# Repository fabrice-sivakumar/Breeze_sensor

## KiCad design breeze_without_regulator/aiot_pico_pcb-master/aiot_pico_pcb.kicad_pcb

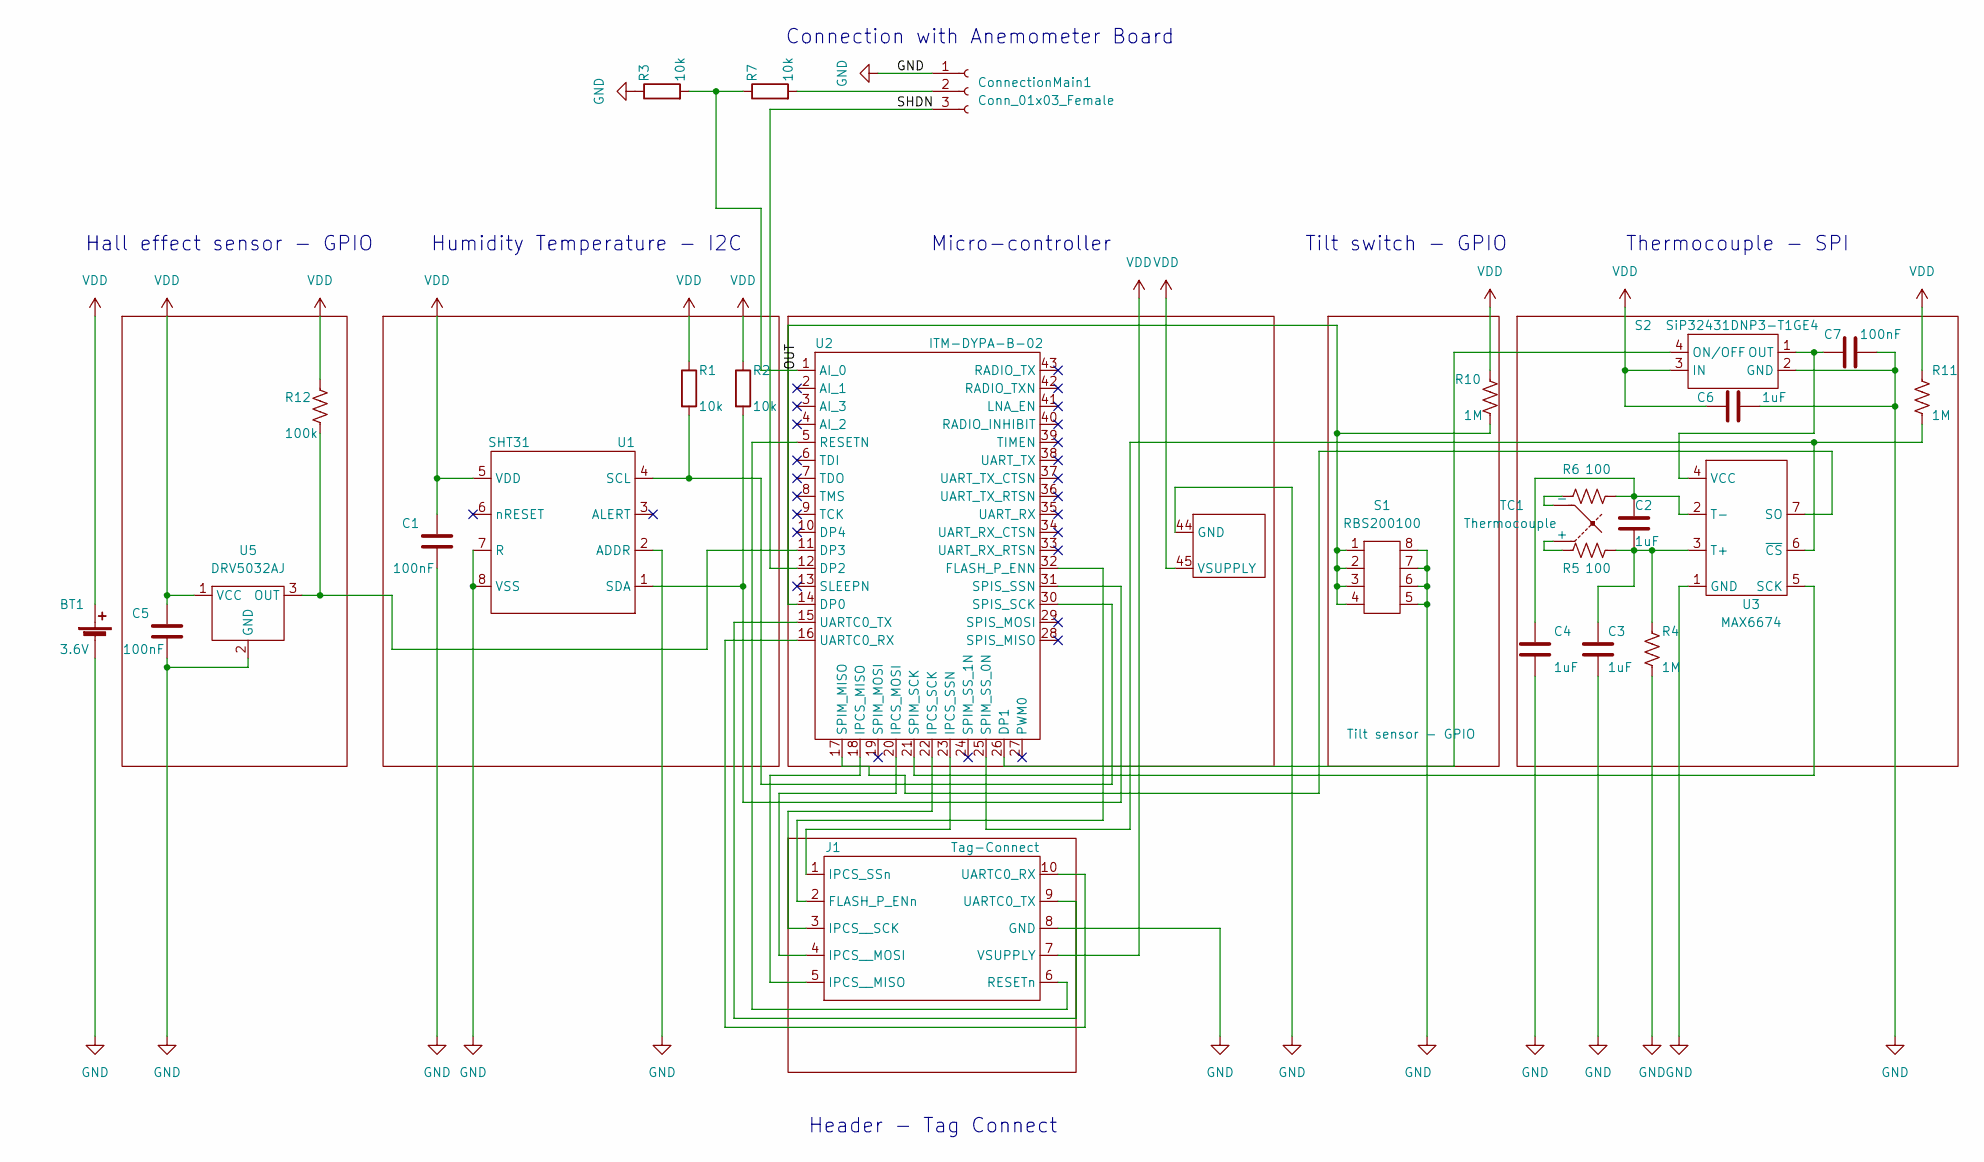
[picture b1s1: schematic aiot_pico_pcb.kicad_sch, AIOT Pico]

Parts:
BT1: 3.6V; BatteryHolder_Keystone_2460_1xAA
C1, C5, C7: 100nF; C_0603_1608Metric
C2, C3, C4, C6: 1uF; C_0603_1608Metric
ConnectionMain1: Conn_01x03_Female; PinSocket_1x03_P2.54mm_Vertical
J1: Tag-Connect; tag-connect_10_pins_no_hooks
R1, R2, R3, R7: 10k; R_0603_1608Metric
R4, R10, R11: 1M; R_0603_1608Metric
R5, R6: 100; R_0603_1608Metric
R12: 100k; R_0603_1608Metric
S1: RBS200100
S2: SiP32431DNP3-T1GE4; TDFN4_1.2mmx1.6mm
TC1: Thermocouple; Thermocouple_Connector_PCC-SMP-K
U1: SHT31; sht_31
U2: ITM-DYPA-B-02; dusty_pcb_ant
U3: MAX6674; SOIC-7-8_W3.9mm
U5: DRV5032AJ; TO-92-3

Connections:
/OUT: R3.2, R7.1, U2.1 (AI_0)
/SHDN: ConnectionMain1.3, U2.12 (DP2)
GND: BT1.2 (-), C1.2, C3.2, C4.2, C5.2, C6.2, C7.1, ConnectionMain1.1, J1.8 (GND), R3.1, R4.2, S1.5, S1.6, S1.7, S1.8, S2.2 (GND), U1.2 (ADDR), U1.7 (R), U1.8 (VSS), U2.44 (GND), U3.1 (GND), U5.2 (GND)
unnamed: C2.1, C4.1, R6.2, U3.2 (T-)
unnamed: C2.2, C3.1, R4.1, R5.2, U3.3 (T+)
unnamed: C7.2, S2.1 (OUT), U3.4 (VCC)
unnamed: ConnectionMain1.2, R7.2
unnamed: J1.1 (IPCS_SSn), U2.23 (IPCS_SSN)
unnamed: J1.2 (FLASH_P_ENn), U2.32 (FLASH_P_ENN)
unnamed: J1.3 (IPCS__SCK), U2.22 (IPCS_SCK)
unnamed: J1.4 (IPCS__MOSI), U2.20 (IPCS_MOSI)
unnamed: J1.5 (IPCS__MISO), U2.18 (IPCS_MISO)
unnamed: J1.6 (RESETn), U2.5 (RESETN)
unnamed: J1.9 (UARTC0_TX), U2.15 (UARTC0_TX)
unnamed: J1.10 (UARTC0_RX), U2.16 (UARTC0_RX)
unnamed: R1.2, U1.4 (SCL), U2.30 (SPIS_SCK)
unnamed: R2.2, U1.1 (SDA), U2.31 (SPIS_SSN)
unnamed: R5.1, TC1.1 (+)
unnamed: R6.1, TC1.2 (-)
unnamed: R10.2, S1.1, S1.2, S1.3, S1.4, U2.14 (DP0)
unnamed: R11.2, U2.25 (SPIM_SS_0N), U3.6 (~CS)
unnamed: R12.2, U2.11 (DP3), U5.3 (OUT)
unnamed: S2.4 (ON/OFF), U2.26 (DP1)
unnamed: U2.17 (SPIM_MISO), U3.7 (SO)
unnamed: U2.21 (SPIM_SCK), U3.5 (SCK)
VDD: BT1.1 (+), C1.1, C5.1, C6.1, J1.7 (VSUPPLY), R1.1, R2.1, R10.1, R11.1, R12.1, S2.3 (IN), U1.5 (VDD), U2.45 (VSUPPLY), U5.1 (VCC)

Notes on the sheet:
Thermocouple - SPI
Hall effect sensor - GPIO
Connection with Anemometer Board
Tilt switch - GPIO
Humidity Temperature - I2C
Micro-controller
Header - Tag Connect

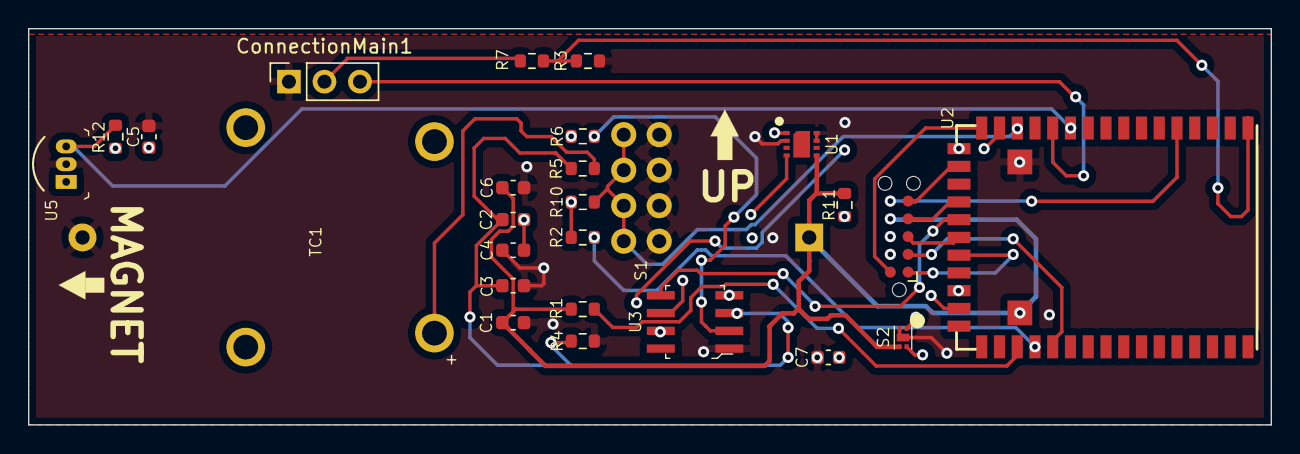
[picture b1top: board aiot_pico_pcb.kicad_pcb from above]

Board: 4 copper layers, 88.9 x 28.3 mm, 27 parts (1 on the bottom side), 26 nets.

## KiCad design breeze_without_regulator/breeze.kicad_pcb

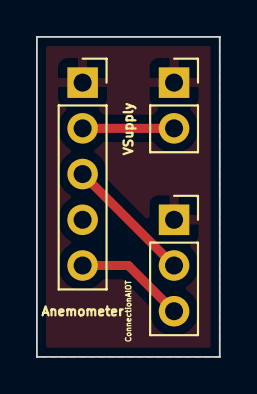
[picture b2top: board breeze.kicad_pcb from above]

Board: 2 copper layers, 10.2 x 17.8 mm, 3 parts (0 on the bottom side), 4 nets.

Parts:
Anemometer: Conn_01x05_Female; PinSocket_1x05_P2.54mm_Vertical
ConnectionAIOT: Conn_01x03_Female; PinSocket_1x03_P2.54mm_Vertical
VSupply: Conn_01x02_Female; PinSocket_1x02_P2.54mm_Vertical

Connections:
/12V: Anemometer.2, VSupply.2
/GND: Anemometer.1, ConnectionAIOT.1, VSupply.1
/OUT: Anemometer.3, ConnectionAIOT.2
/SHDN: Anemometer.5, ConnectionAIOT.3

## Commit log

2023-06-22 Codes
2023-07-06 US_experiments
